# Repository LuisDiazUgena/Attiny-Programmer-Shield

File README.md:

# Attiny-Programmer-Shield

Create your own Attiny Programmer Shield!

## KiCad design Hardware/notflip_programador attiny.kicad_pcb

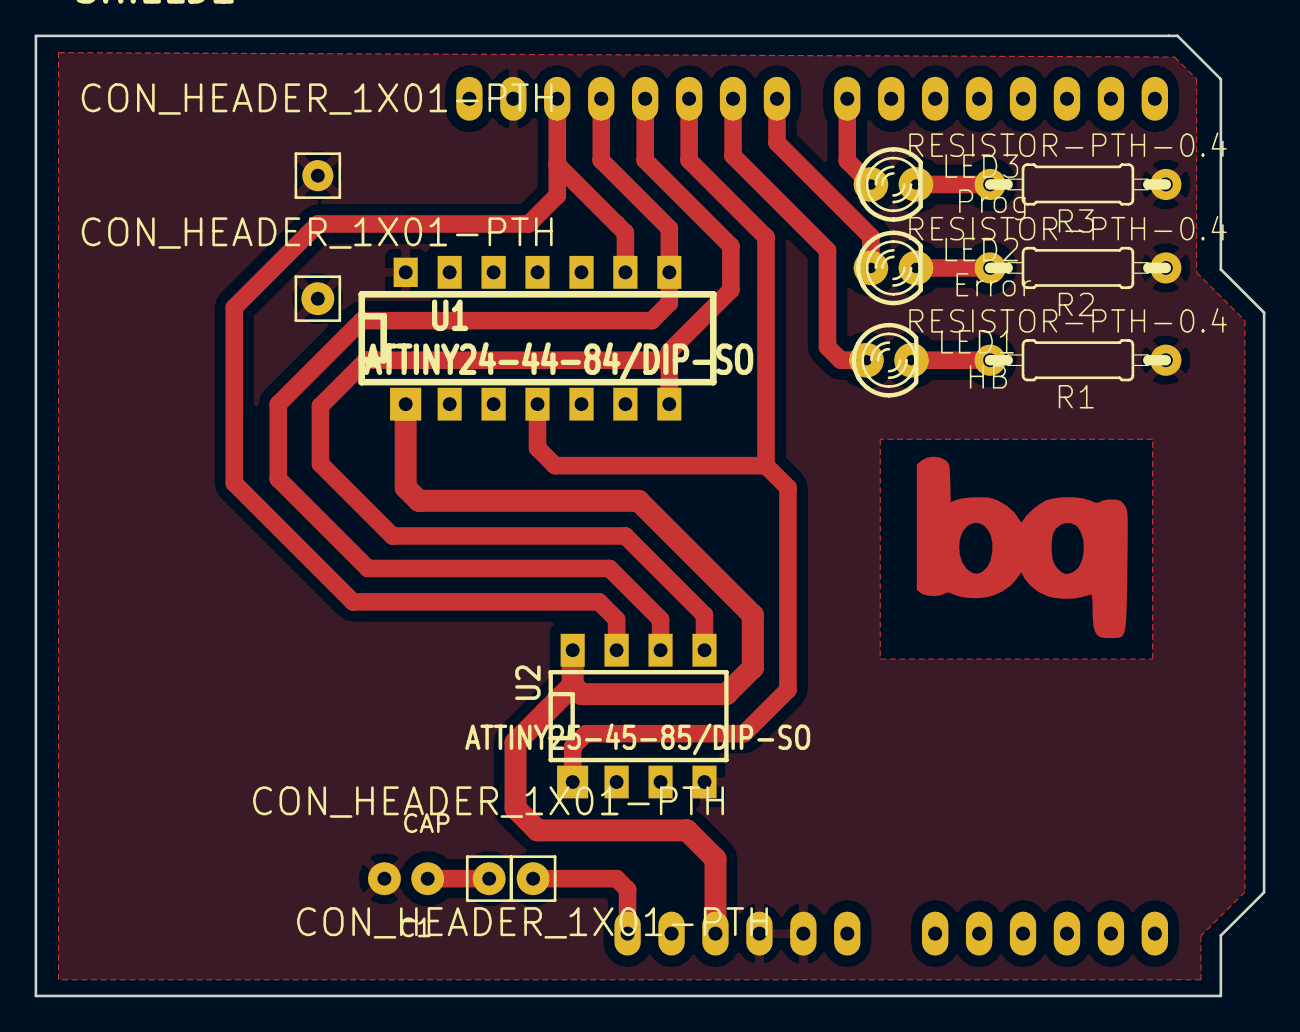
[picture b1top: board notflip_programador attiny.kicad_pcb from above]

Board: 2 copper layers, 71.0 x 55.5 mm, 14 parts (0 on the bottom side), 14 nets.

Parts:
C1: CAP; Cap_troughHole
J1, J2, J3, J4: CON_HEADER_1X01-PTH; dp_devices-M1X1
LED1: HB; Led_3mm_bigger_pads
LED2: Error; Led_3mm_bigger_pads
LED3: Prog; Led_3mm_bigger_pads
R1, R2, R3: RESISTOR-PTH-0.4; dp_devices-RTH025W
SHIELD1: ARDUINO_SHIELD; ARDUINO_SHIELD_2
U1: ATTINY24-44-84/DIP-SO; DIP-14__300
U2: ATTINY25-45-85/DIP-SO; DIP-8__300

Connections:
unnamed: LED1.A, SHIELD1.9
unnamed: LED2.A, SHIELD1.8
unnamed: LED3.A, SHIELD1.7
unnamed: LED3.K, R3.2
unnamed: LED2.K, R2.2
unnamed: LED1.K, R1.2
unnamed: C1.1, J3.1
unnamed: J4.1, SHIELD1.RST
unnamed: SHIELD1.10, U1.4, U2.1
unnamed: SHIELD1.11, U1.7, U2.5
unnamed: SHIELD1.13, U1.9, U2.7
unnamed: SHIELD1.12, U1.8, U2.6
gnd: C1.2, J1.1, J2.1, R1.1, R2.1, R3.1, SHIELD1.GND1, SHIELD1.GND2, SHIELD1.GND3, U1.14, U2.4
vcc: SHIELD1.5V, U1.1, U2.8

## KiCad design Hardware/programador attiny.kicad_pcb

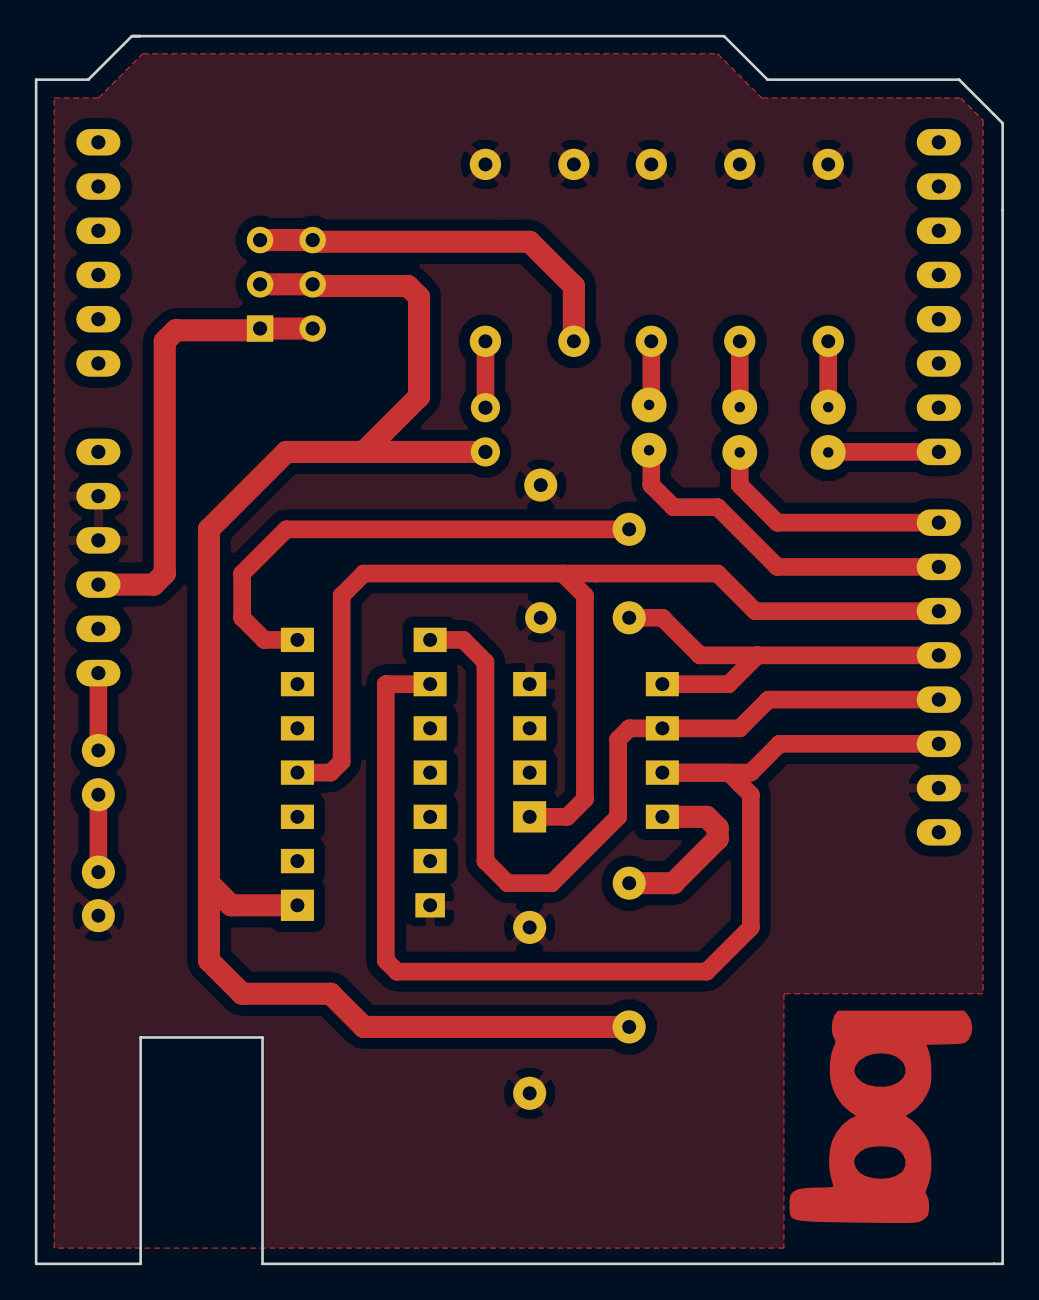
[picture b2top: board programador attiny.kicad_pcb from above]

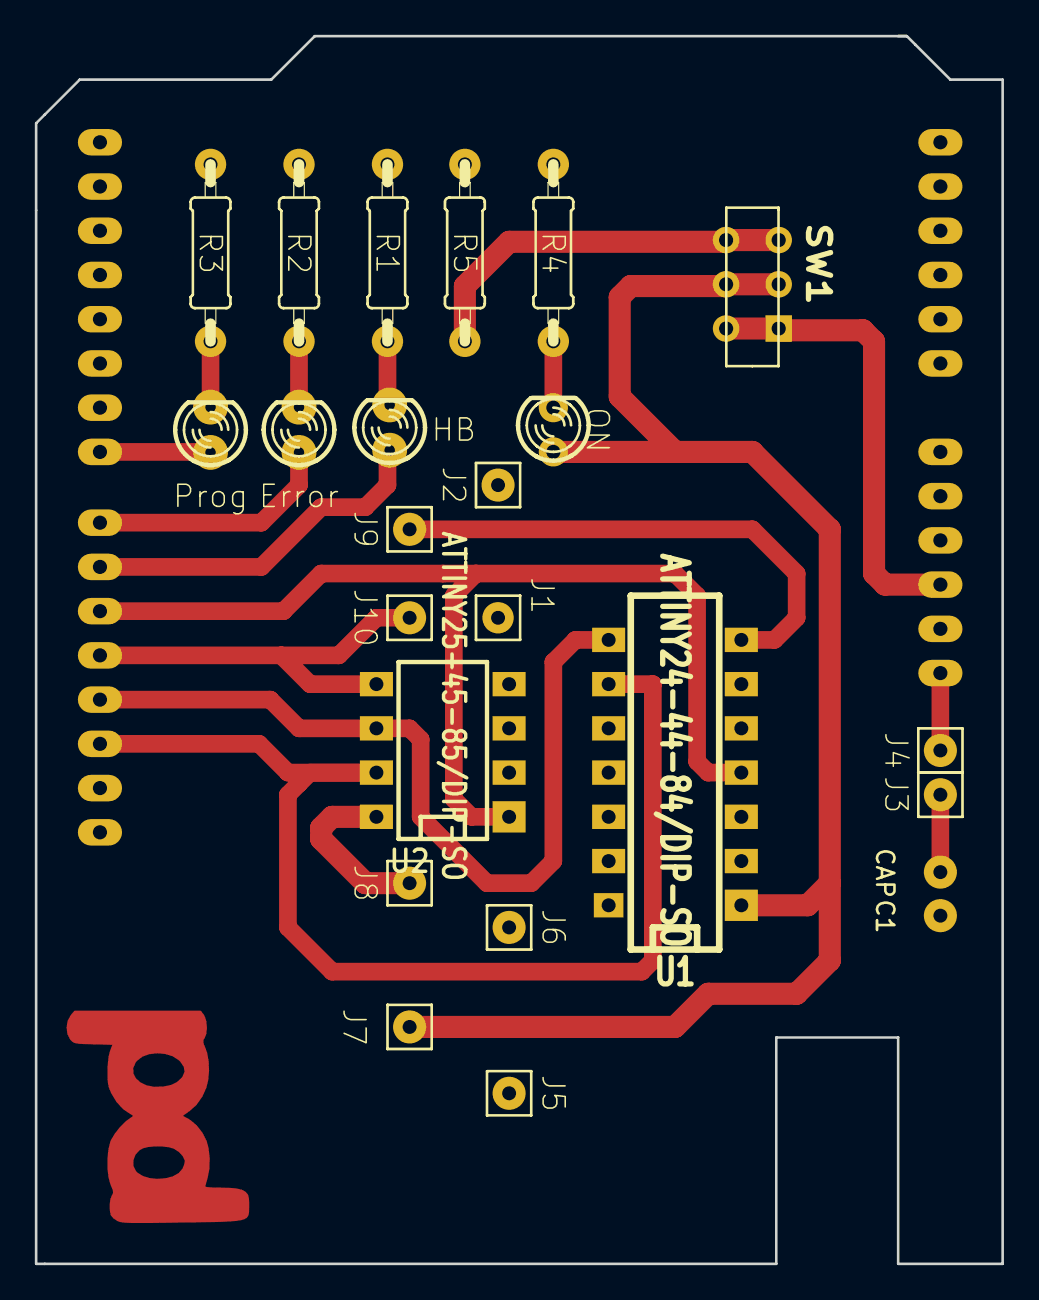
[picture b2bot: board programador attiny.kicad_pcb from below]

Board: 2 copper layers, 55.5 x 70.5 mm, 19 parts (19 on the bottom side), 9 nets.

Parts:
C1: CAP; Cap_troughHole
J1, J2, J3, J4, J5, J6, J7, J8, J9, J10: dp_devices-M1X1
R1, R2, R3, R4, R5: dp_devices-RTH025W
SW1: SWITCH; swdip3
U1: ATTINY24-44-84/DIP-SO; DIP-14__300
U2: ATTINY25-45-85/DIP-SO; DIP-8__300

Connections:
unnamed: U1.8, U2.6
unnamed: J9.1, J10.1, U1.7, U2.5
unnamed: R5.1, SW1.3, SW1.5
unnamed: SW1.1, SW1.6
unnamed: U1.9, U2.7
unnamed: C1.1, J3.1
unnamed: U1.4, U2.1
gnd: C1.2, J1.1, J2.1, J5.1, J6.1, R1.1, R2.1, R3.1, R4.1, R5.2, U1.14, U2.4
vcc: J7.1, J8.1, SW1.2, SW1.4, U1.1, U2.8

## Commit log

2015-08-20 Added all files
2015-08-20 Added picture of the shield
2015-08-20 Added shield picture
2017-03-22 Added schematic
